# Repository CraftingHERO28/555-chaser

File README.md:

555 Mountain LED Chaser

Welcome to my Hack Club Forge project!

I wanted to build something a bit more interesting than a basic blinking LED—a circuit where light smoothly runs through a sequence. That’s how this LED chaser came to life! It’s powered by a classic NE555 timer chip to generate the clock signal and a 4017 counter chip that lights up each LED one after another.

#Why a mountain shape?

I really didn't want to make just another standard rectangular board. I love nature and spend a lot of time outdoors, so I decided to draw the PCB outline in the shape of a mountain range. The LEDs are placed along the peaks, so when they light up in sequence, it looks like a trail of light moving across the mountains.

#How it works

Clock Generator: The NE555 timer is wired in astable mode to create a pulse signal. You can adjust the speed of the chasing light using the potentiometer.

Decade Counter: The CD4017 chip takes those clock pulses and turns on the output pins one by one, lighting up each LED.

Power: The whole board runs on 5V, supplied through a simple 2-pin header (I'm using a modified USB cable for this).

#The biggest challenges

Designing this board came with a few tricky parts:

Routing inside a mountain shape: Since the board isn't a simple square, routing all the copper traces without running out of room felt like a giant puzzle.

Staying within the board edge: I had to make sure no traces or components got too close to the edge cutouts of the mountain peaks to avoid any shorts or manufacturing issues.

It took quite a bit of patience to get all the tracks placed cleanly, but I'm really happy with how the final layout turned out!

#Bill of Materials (BOM)

The complete list of components, prices, and purchasing links can be found in the BOM.csv file in this repository.

#Gallery & PCB Preview

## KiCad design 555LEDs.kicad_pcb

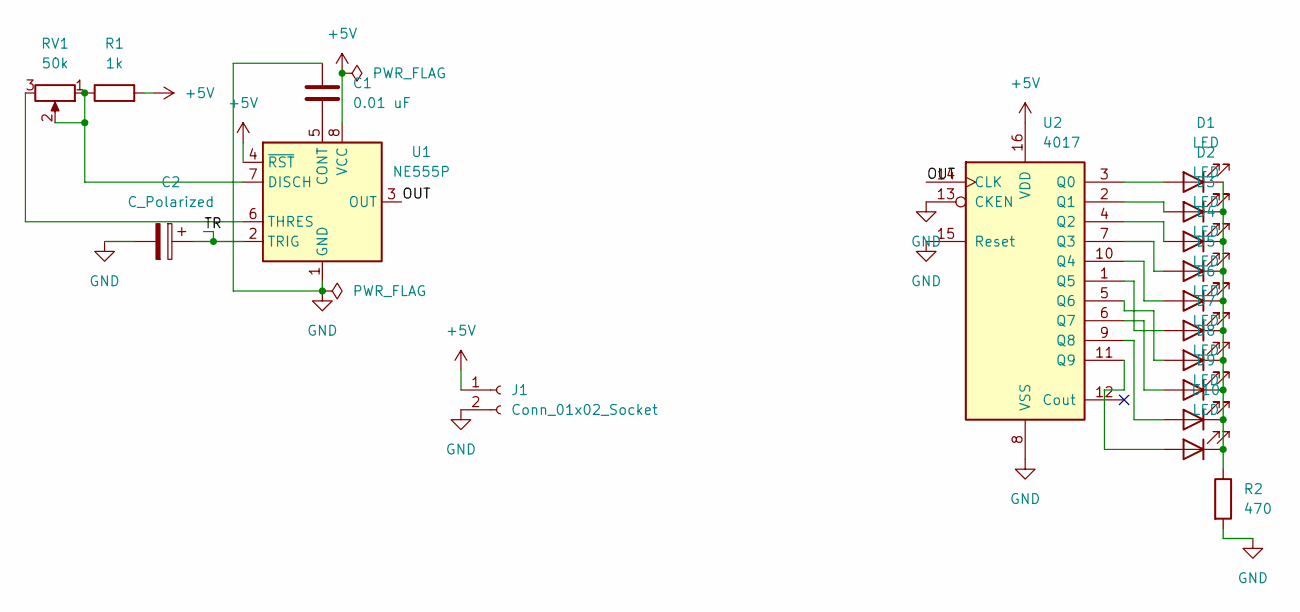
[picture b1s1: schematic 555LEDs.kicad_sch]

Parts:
C1: 0.01 uF; CP_Radial_D5.0mm_P2.00mm
C2: C_Polarized; C_Disc_D7.5mm_W2.5mm_P5.00mm
D1, D2, D3, D4, D5, D6, D7, D8, D9, D10: LED; LED_D3.0mm
J1: Conn_01x02_Socket; PinHeader_1x02_P2.54mm_Vertical
R1: 1k; R_Axial_DIN0207_L6.3mm_D2.5mm_P7.62mm_Horizontal
R2: 470; R_Axial_DIN0207_L6.3mm_D2.5mm_P7.62mm_Horizontal
RV1: 50k; Potentiometer_Alps_RK09K_Single_Vertical
U1: NE555P; DIP-8_W7.62mm
U2: 4017; DIP16

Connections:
+5V: J1.1, R1.2, U1.4 (~RST), U1.8 (VCC), U2.16 (VDD)
/OUT: U1.3 (OUT), U2.14 (CLK)
/TR: C2.1, U1.2 (TRIG)
GND: C1.2, C2.2, J1.2, R2.2, U1.1 (GND), U2.8 (VSS), U2.13 (CKEN), U2.15 (Reset)
unnamed: D1.2 (A), U2.3 (Q0)
unnamed: D1.1 (K), D2.1 (K), D3.1 (K), D4.1 (K), D5.1 (K), D6.1 (K), D7.1 (K), D8.1 (K), D9.1 (K), D10.1 (K), R2.1
unnamed: D2.2 (A), U2.2 (Q1)
unnamed: D3.2 (A), U2.4 (Q2)
unnamed: D4.2 (A), U2.7 (Q3)
unnamed: D5.2 (A), U2.10 (Q4)
unnamed: D6.2 (A), U2.1 (Q5)
unnamed: D7.2 (A), U2.5 (Q6)
unnamed: D8.2 (A), U2.6 (Q7)
unnamed: D9.2 (A), U2.9 (Q8)
unnamed: D10.2 (A), U2.11 (Q9)
unnamed: C1.1, U1.5 (CONT)
unnamed: R1.1, RV1.1, RV1.2, U1.7 (DISCH)
unnamed: RV1.3, U1.6 (THRES)

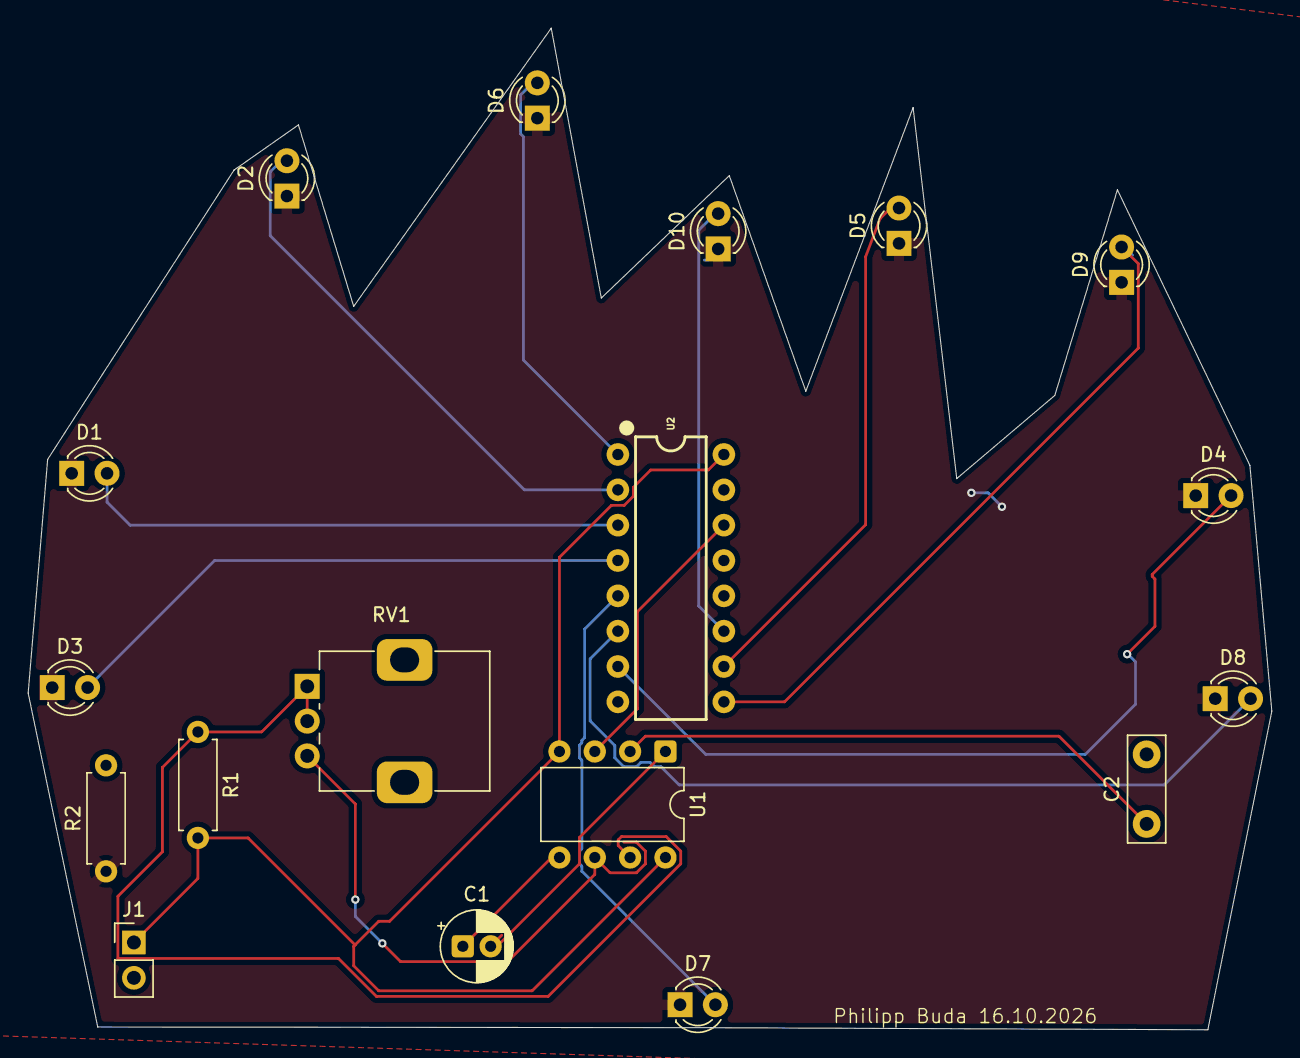
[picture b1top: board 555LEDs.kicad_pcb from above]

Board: 2 copper layers, 89.4 x 72.0 mm, 18 parts (0 on the bottom side), 18 nets.
